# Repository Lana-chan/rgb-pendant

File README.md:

RGB Pendant
===========

These are the source files (schematic and code) for a color-changing trinket, originally designed to be used as a necklace pendant.
The design is based off an ATtiny85 and a generic common-cathode RGB LED.

The boards have been done in EAGLE 7.1.0 Light and KiCad (2013-07-07BZR 4022)-stable and as of this commit have not yet been tested for manufacture, but they have no design-rule errors.
To compile the code with the Arduino IDE, you need the following:
* ATtiny cores: https://code.google.com/p/arduino-tiny/
* WinAVR Linker bugfix: http://forum.arduino.cc/index.php/topic,116674.0.html

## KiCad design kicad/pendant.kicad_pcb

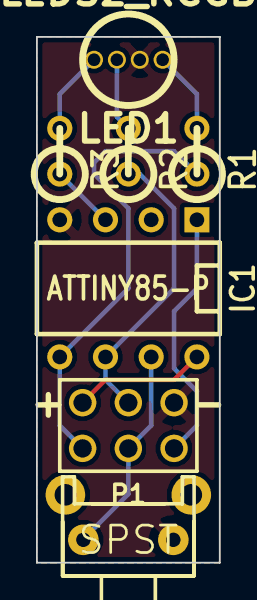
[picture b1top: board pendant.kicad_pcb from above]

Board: 2 copper layers, 10.2 x 29.2 mm, 7 parts (0 on the bottom side), 10 nets.

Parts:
IC1: ATTINY85-P; DIP-8__300
LED1: LEDS2_RCGB; LED5_RGB
P1: CONN_3X2; pin_array_3x2
R1, R2, R3: R; R1
SW1: SPST; SparkFun-Electromechanical-TACTILE-PTH-SIDE

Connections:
+3.3V: IC1.8, P1.5
/BLUE: IC1.3, R3.1
/MISO: IC1.6, P1.3, R2.1
/MOSI: IC1.5, P1.6, R1.1
/RESET: IC1.1, P1.2
/SCK: IC1.7, P1.4, SW1.1
GND: IC1.4, LED1.2, P1.1, SW1.2
unnamed: LED1.1, R1.2
unnamed: LED1.4, R3.2
unnamed: LED1.3, R2.2

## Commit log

2014-10-26 ATtiny85-powered color-changing pendant
    These are the source files (schematic and code) for a color-changing
    trinket, originally designed to be used as a necklace pendant.
2014-10-26 Board slightly reduced in size, silkscreen improved
2014-10-27 Made the board yet smaller
2014-10-27 fixed back silkscreen
2014-10-27 replacing ATtiny part with SparkFun version for standardizing
2014-10-27 thicker routes
2014-11-09 redone routes and replaced resistor type
2014-11-09 created kicad version of the board
2014-12-08 silkscreen improvement
2014-12-11 fixing ICSP header
2016-06-12 case fix
